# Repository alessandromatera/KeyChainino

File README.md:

# KeyChainino

KeyChainino is the first keychain you can program with Arduino: a tiny game
console with an LED matrix, two buttons and a coin cell. This repo holds
the open-source firmware for every KeyChainino, plus an in-browser
simulator of the KeyChainino 144.

More at [keychainino.com](https://www.keychainino.com).

## Boards and sketches

| Folder | Board |
|---|---|
| `Sketch/KeyChainino_v4_144_LEDs/` | **KeyChainino 144**: ATmega328P, 12×12 LEDs (the current board) |
| `Sketch/KeyChainino_v3_64_LEDs/` | KeyChainino v3: ATmega328P, 8×8 LEDs |
| `Sketch/KeyChainino_v1_&_THT/`, `Sketch/Tutorial-WALLED/` | The original KeyChainino and the through-hole kit (THT), 5×6 LEDs |
| `THT/`, `Schematic/` | THT kit schematics and board files |

### KeyChainino 144

Every sketch folder is self-contained, with no library to install:

| Sketch | What it is |
|---|---|
| `KeyChainino_v144_multigame` | The 17-game firmware with a menu: Bricks, Snake, Blocks, Invaders, Tennis, Tower, Frog, Flap, Racer, Echo, Jump, Catch, Whack, Dice, Life, Muncher and Steroids |
| `KeyChainino_v144_bubble` | Bubble shooter |
| `KeyChainino_v144_snake` | Snake, standalone |
| `KeyChainino_v144_quest` | An adventure across 16 rooms: find the sword and two keys, then beat the dungeon boss |
| `KeyChainino_v144_pictures` | A picture book for small children, with a web page where they draw their own pictures and send them to the KeyChainino |
| `KeyChainino_v4_conta_punti` | Stitch and row counter for knitting and sewing |
| `KeyChainino_pet` | A virtual pet to feed, clean and play with |
| `KeyChainino_watch` | A clock: A+B shows the time |
| `test_charlie` | LED matrix test |

## Building and flashing

The 144 is programmed over ISP (e.g. a USBasp). With
[arduino-cli](https://arduino.github.io/arduino-cli/):

```sh
arduino-cli compile --fqbn arduino:avr:pro:cpu=8MHzatmega328 \
  --output-dir build Sketch/KeyChainino_v4_144_LEDs/KeyChainino_v144_multigame

avrdude -patmega328p -cusbasp -Pusb \
  -U lfuse:w:0xe2:m -U hfuse:w:0xd7:m -U efuse:w:0xff:m \
  -U flash:w:build/KeyChainino_v144_multigame.ino.hex:i
```

See [`docs/DEVELOPMENT.md`](docs/DEVELOPMENT.md) for the hardware limits
and how the sketch folders are organized.

## Simulator

Open `simulator/index.html` in a browser to play the KeyChainino 144
without hardware. It runs the real compiled firmware, and you can drop
your own `.hex` onto it. See [`simulator/README.md`](simulator/README.md).

## License

GPL-2.0. See [LICENSE](LICENSE). The LED driver bundled with the pet
and watch sketches derives from SparkFun's 8×7 Charlieplex LED Array
library, and the scrolling text uses SparkFun's "Font 1". Both are
public domain (Beerware).

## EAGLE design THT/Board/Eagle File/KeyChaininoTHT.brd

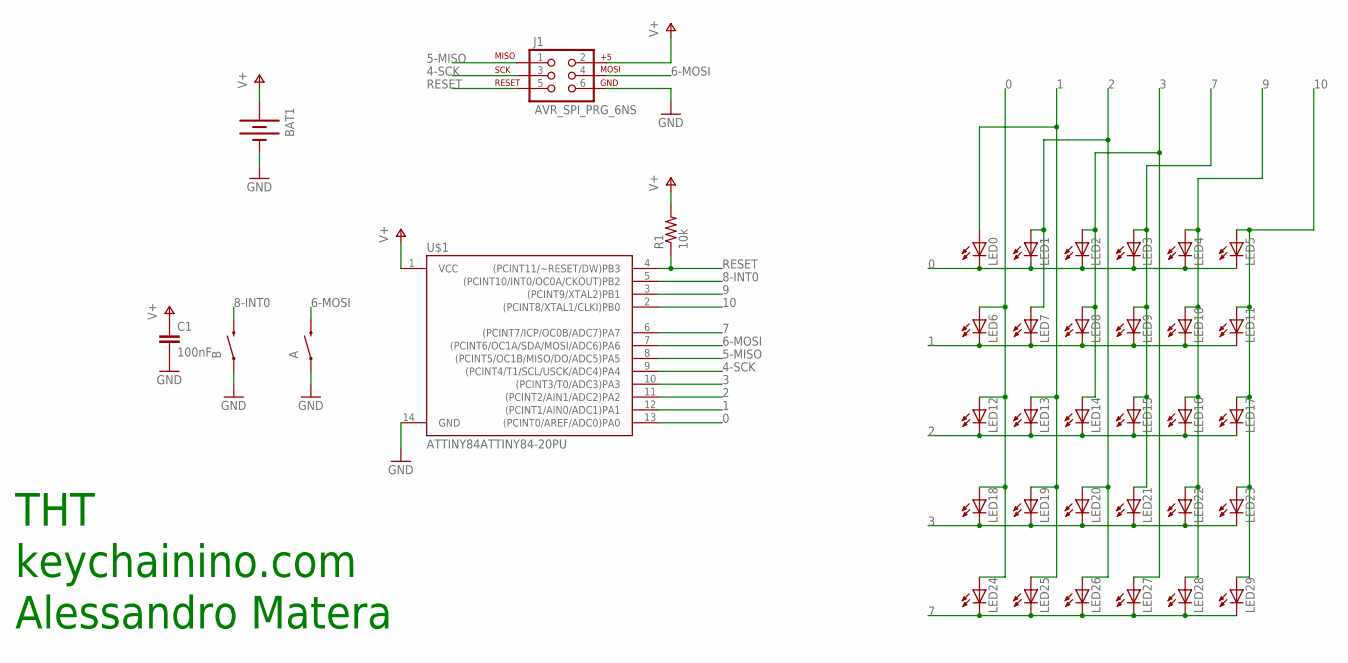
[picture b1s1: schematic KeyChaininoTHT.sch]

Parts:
A: SWITCH-MOMENTARY-2PTH; TACTILE-PTH
B: SWITCH-MOMENTARY-2PTH; TACTILE-PTH
BAT1: BATTERY20PTH; BATTCOM_20MM_PTH
C1: 100nF; CAP-PTH-SMALL-KIT
J1: AVR_SPI_PRG_6NS; 2X3-NS
LED0, LED1, LED2, LED3, LED4, LED5, LED6, LED7, LED8, LED9, LED10, LED11, LED12, LED13, LED14, LED15, LED16, LED17, LED18, LED19, LED20, LED21, LED22, LED23, LED24, LED25, LED26, LED27, LED28, LED29: LED3MM
R1: 10k; AXIAL-0.3-KIT
U$1: ATTINY84ATTINY84-20PU; DIL14

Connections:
0: LED0.K (C), LED1.K (C), LED2.K (C), LED3.K (C), LED4.K (C), LED5.K (C), LED6.A, LED12.A, LED18.A, LED24.A, U$1.13 ((PCINT0/AREF/ADC0)PA0)
1: LED0.A, LED6.K (C), LED7.K (C), LED8.K (C), LED9.K (C), LED10.K (C), LED11.K (C), LED13.A, LED19.A, LED25.A, U$1.12 ((PCINT1/AIN0/ADC1)PA1)
2: LED1.A, LED7.A, LED12.K (C), LED13.K (C), LED14.K (C), LED15.K (C), LED16.K (C), LED17.K (C), LED20.A, LED26.A, U$1.11 ((PCINT2/AIN1/ADC2)PA2)
3: LED2.A, LED8.A, LED14.A, LED18.K (C), LED19.K (C), LED20.K (C), LED21.K (C), LED22.K (C), LED23.K (C), LED27.A, U$1.10 ((PCINT3/T0/ADC3)PA3)
4-SCK: J1.3, U$1.9 ((PCINT4/T1/SCL/USCK/ADC4)PA4)
5-MISO: J1.1, U$1.8 ((PCINT5/OC1B/MISO/DO/ADC5)PA5)
6-MOSI: A.3 (2), J1.4, U$1.7 ((PCINT6/OC1A/SDA/MOSI/ADC6)PA6)
7: LED3.A, LED9.A, LED15.A, LED21.A, LED24.K (C), LED25.K (C), LED26.K (C), LED27.K (C), LED28.K (C), LED29.K (C), U$1.6 ((PCINT7/ICP/OC0B/ADC7)PA7)
8-INT0: B.3 (2), U$1.5 ((PCINT10/INT0/OC0A/CKOUT)PB2)
9: LED4.A, LED10.A, LED16.A, LED22.A, LED28.A, U$1.3 ((PCINT9/XTAL2)PB1)
10: LED5.A, LED11.A, LED17.A, LED23.A, LED29.A, U$1.2 ((PCINT8/XTAL1/CLKI)PB0)
GND: A.1, B.1, BAT1.2 (-), C1.2, J1.6, U$1.14 (GND)
RESET: J1.5, R1.P$1 (1), U$1.4 ((PCINT11/~RESET/DW)PB3)
V+: BAT1.1 (+), C1.1, J1.2, R1.P$2 (2), U$1.1 (VCC)

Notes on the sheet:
THT
keychainino.com
Alessandro Matera

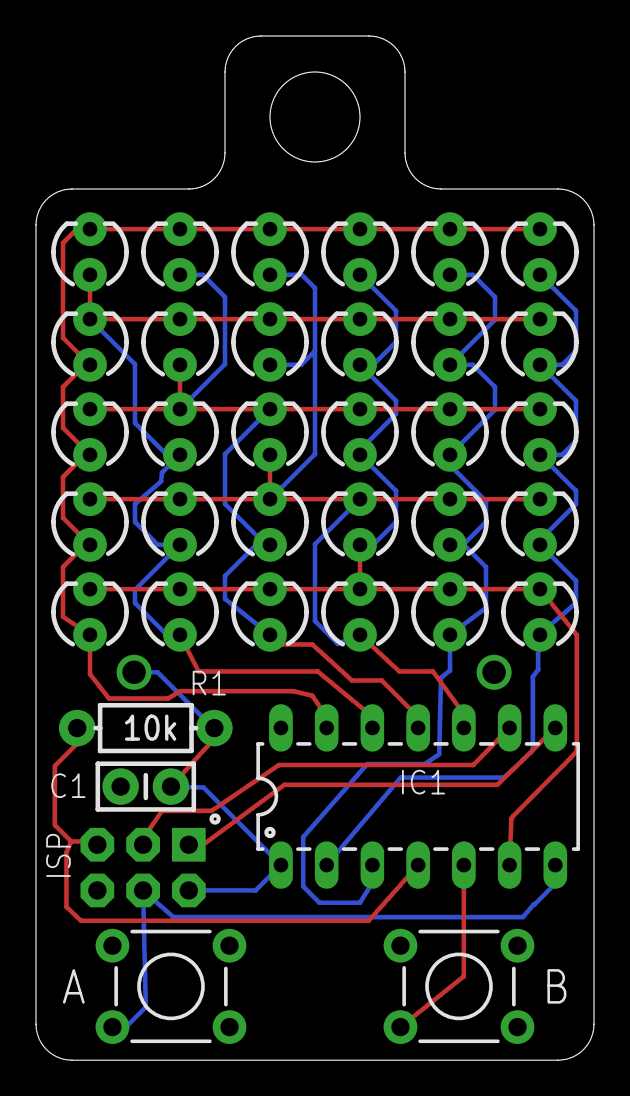
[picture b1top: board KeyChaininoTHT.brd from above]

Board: 2 copper layers, 31.0 x 56.9 mm, 37 parts (1 on the bottom side), 14 nets.

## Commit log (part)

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2015-12-04 added sketch
2015-12-04 added comment
2015-12-05 added KeyChainino Face
2015-12-05 fixes
2015-12-07 new text scrolling sketch
2015-12-15 Changed Charlieplexing frequency to 60 Hz, by set the timer1 interflow interrupt.
2015-12-16 new method to show score
2015-12-17 added jump game
2015-12-19 V 1.1
    - fixed the way ball touch the bar:
    previously the ball disappear, now it bouncing on the bar.
    - new way to start the game:
    previously you need to press al least one button to start to play.
    Now you must press the two button at the same time. It is due for save
    energy and for not start the game involuntarily.
2015-12-20 - added new sketch for Christmas - Jump game fixes
2015-12-20 fixed charlieplexing
2015-12-20 added new lamp sketch
2015-12-30 added description
2015-12-30 New game: walled
2016-01-03 Basic Sketch structure for make your own game
2016-01-03 Walled tutorial part 1
2016-01-10 modified bitSet
2016-01-10 New Game Tap in time
2016-01-11 TUTORIAL WALLED 3
2016-01-17 tutorial walled part 4
2016-01-24 added KeyChainino Schematic
2016-02-14 S_Valentine sketch
2016-02-24 Dice game + library entropy
2016-03-03 THT board and schematics
2016-04-09 changed Delay on Charlieplexing
2016-05-14 new sketch
2016-10-30 sketch
2016-11-06 THT v2
2016-11-17 new sketch HeadsOrTails
2016-12-03 added set and clear matrixState bit functions
    //here we set or clear a single bit on the matrixState. We use this
    funciton in order
    //to really set or clear the matrix's bit when an interrupt occours. To
    do that we disable the
    //interrupt -> set or clear the bit -> enable interrupt
    void setMatrixStateBit(byte i, byte j) {
2017-04-29 Added sketches for KeyChainino USB
2017-04-29 name fix
2017-11-02 fixed autostart
2017-11-02 phrase on top
2019-01-13 added dice 2 sketch
2019-09-21 Update Sketches
    Update sketches with new charlieplexing technique and bug fixes
2019-09-23 new scrolling sketch
2019-11-03 Added PWM
2019-11-03 bug fixes
2019-12-08 update Sketch directory
2019-12-08 fixed some sketches directory
2021-06-26 V144 sketches added + library
2025-01-20 fix library to improve battery life in power down
2025-04-06 new keychainino 144 sketches
2025-05-16 Ported for KC 144

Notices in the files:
parts and their libraries:
SparkFun-Electromechanical: Licensing: CC v3.0 Share-Alike You are welcome to use this library for commercial purposes.
